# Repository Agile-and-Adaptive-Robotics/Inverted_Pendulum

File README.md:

# Inverted Pendulum

This repository contains the files related to the development, construction, and testing of the pneumatically-actuated Inverted Pendulum experimental rig, by members of the Agile & Adaptive Robotics Laboratory at Portland State University. The Inverted Pendulum was developed in tandem with the [Balance Platform](https://github.com/Agile-and-Adaptive-Robotics/Balance_Platform). The pair represents an experimental testbed for exploring perturbed bipedal stance, and was inspired by Peterka, 2002.

Note that this repo is for the pitured version of the Inverted Pendulum. The previous repo was archived and can be accessed [here] (https://github.com/Agile-and-Adaptive-Robotics/Inverted_Pendulum-archive). 

## Contents

- [Software](/code)
  - [README](/code/README.md)
- [datasheets](/datasheets)
  - [README](/datasheets/README.md)
- [pics](/pics)
- [SolidWorks](/SolidWorks)

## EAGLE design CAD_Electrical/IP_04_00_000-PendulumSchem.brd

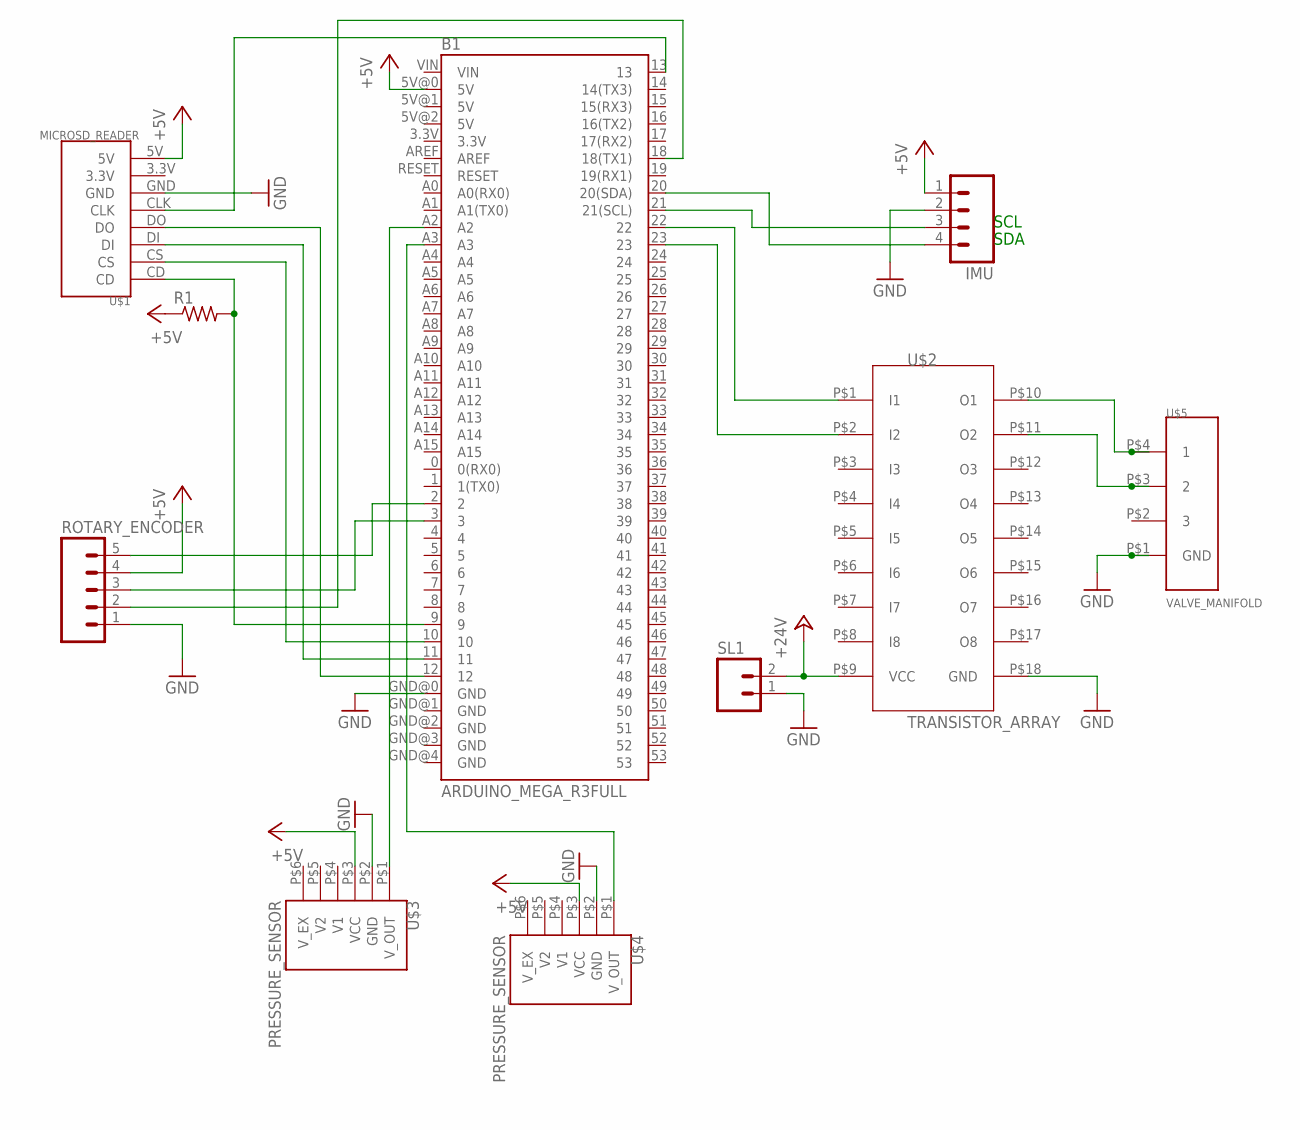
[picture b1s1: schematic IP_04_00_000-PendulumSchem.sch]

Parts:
B1: ARDUINO_MEGA_R3FULL; ARDUINO_MEGA
IMU: M04; 04P
R1: R-US_0204/7; 0204/7
ROTARY_ENCODER: M05; 05P
SL1: M02; 02P
U$1: MICROSD_READER
U$2: TRANSISTOR_ARRAY
U$3, U$4: PRESSURE_SENSOR
U$5: VALVE_MANIFOLD

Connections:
+5V: B1.5V@0 (5V), IMU.1, R1.1, ROTARY_ENCODER.4, U$1.5V, U$3.P$3 (VCC), U$4.P$3 (VCC)
+24V: SL1.2, U$2.P$9 (VCC)
GND: B1.GND@0 (GND), IMU.2, ROTARY_ENCODER.1, SL1.1, U$1.GND, U$2.P$18 (GND), U$3.P$2 (GND), U$4.P$2 (GND), U$5.P$1 (GND)
unnamed: B1.3, ROTARY_ENCODER.3
unnamed: B1.20 (20(SDA)), IMU.4
unnamed: B1.21 (21(SCL)), IMU.3
unnamed: B1.2, ROTARY_ENCODER.5
unnamed: B1.22, U$2.P$1 (I1)
unnamed: U$2.P$10 (O1), U$5.P$4 (1)
unnamed: B1.18 (18(TX1)), ROTARY_ENCODER.2
unnamed: U$2.P$11 (O2), U$5.P$3 (2)
unnamed: B1.23, U$2.P$2 (I2)
unnamed: B1.13, U$1.CLK
unnamed: B1.A2, U$3.P$1 (V_OUT)
unnamed: B1.12, U$1.DO
unnamed: B1.A3, U$4.P$1 (V_OUT)
unnamed: B1.11, U$1.DI
unnamed: B1.10, U$1.CS
unnamed: B1.9, R1.2, U$1.CD

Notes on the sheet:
SCL
SDA

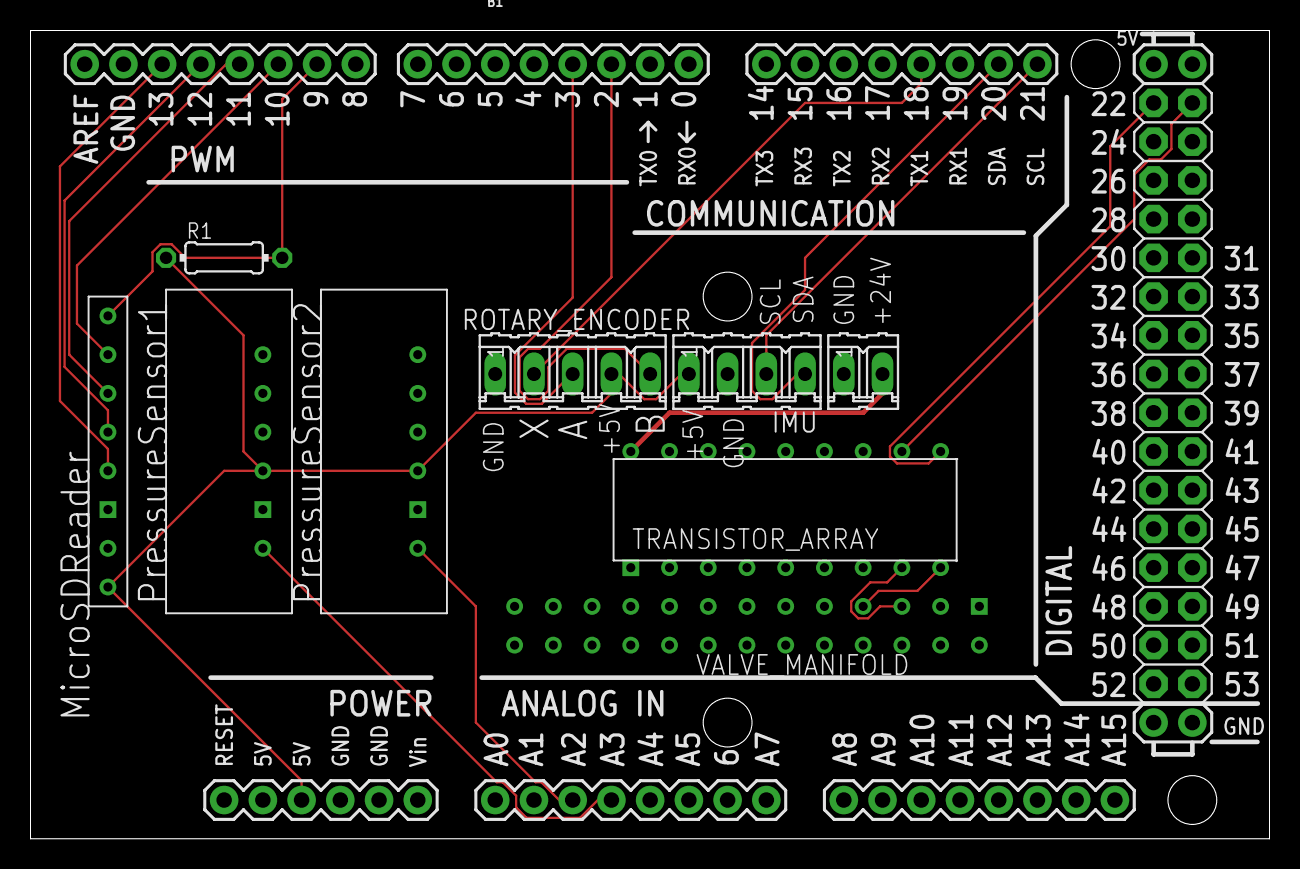
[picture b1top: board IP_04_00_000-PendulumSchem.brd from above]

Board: 2 copper layers, 81.3 x 53.0 mm, 10 parts (1 on the bottom side), 19 nets.

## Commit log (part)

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2020-06-13 Initial commit.
2020-06-14 Added DELETEME files.
2020-06-17 Added CAD assembly structures.
2020-06-17 Created basic foot base for designing main ankle joint.
    Will probably need to revise diameters? Appears to have odd proportions
2020-06-17 Same dimensions, split in half to fit on build plate (12in by 5in direction)
    In assembly, mirror around plane 1 from this part to get full build plate
2020-06-17 Created potential spool part
    This was mostly made as practice, very likely to change
2020-06-17 Fixed units to metric and extruded cuts for disc break
2020-06-17 McMaster-Carr hex bolt for base to balance plate
2020-06-17 Created tilapia joint, added mounting holes for tilapia to joint
2020-06-18 Added pulley for tendon string plus spool
2020-06-18 Modeled latch for disk break
    will need to decide if controlled by servo or switch before I create the rest of the mount. Also, will need gears to move string spool (& change shaft of spring to hex)
2020-06-18 Modified string spool to bevel gear top
    Removed disc brake because at such a small scale & low power, not necessary. Now can be controllable with rotary shaft & bevel gear
2020-06-18 Changed relations in independent bevel gear
2020-06-18 Switched sides for pulley mount
    This was done so that the tendon strings do not rub against the main shaft
2020-06-18 Created new tipia assembly, slotted tipia, added mounting holes to joint
2020-06-19 Began on double-axis attachment
    Explored two other somewhat feasible options for moveable attachments but could foresee that they added unnecessary complexity when moving into 2D adjustments
2020-06-19 Completed 1-axis adjustable attachment, prepared mounting piece for double axis
2020-06-19 Started vertical adjustment attachment
    Mostly done, will fill in mounting holes, shaft collars, etc. but for the most part ready for BPA CAD mount
2020-06-19 Added shaft collars to horizontal adjustment, shortened vertical shafts
    The more I design the vertical adjustment subassembly, the more I am convinced that I'll need to replace it with a threaded rod. Same concept but will be able to withstand gravity better, assuming th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
2020-06-22 Threaded rod adjustable attachments completed for 2-axis
    Still need to create mount for BPA to attachment piece. Also might shrink height of horizontal piece (unnecessarily bulky)
2020-06-22 Added mounting holes for attachment assembly
2020-06-23 Restored past progress from old bpaMount branch
    Changed type of lock nut to external teeth, inserted the BPA fitting into assembly
2020-06-23 Accidentally committed temporary files again
2020-06-23 Mounting holes and bolts
    Inserted threaded rod into BPA mount with nuts on ends. Reviewed mounting holes and fillets on all parts, and inserted all bolts (except fasteners to balance platform)
2020-06-23 Shifted tendon pulleys so no longer conflicting with attachment assembly
2020-06-23 Fixed locally referenced file
2020-06-25 Attached BPA attachment to sliding adjustment
2020-06-25 replaced round slider with square
2020-06-25 Replaced round slot with square slot
2020-06-28 Created IP assembly, fixed major tibia joint to fit with major foot joint, adjusted tibia mounting holes accordingly
2020-06-29 Added IMU symbol to schem
2020-06-29 Added servos to control tendon spool gear
2020-06-29 resolve conflicting files by copying these files from master
2020-06-29 Added transistory array & valve manifold datasheets.
2020-06-30 Inserted transistor array between arduino & valve manifold
2020-06-30 Added pressure sensor & IMU datasheets.
2020-06-30 Pressure sensors wired on A0, A1
2020-07-01 Disc brake for servo spool
2020-07-01 Servo mount
    Also deleted temp files
2020-07-01 Arduino Mount ATMEGA2560
2020-07-01 Servo mounting & servo files
2020-07-01 Began arduino mount with standoffs
2020-07-01 Finished arduino standoff spacing. Need to insert fasteners & possibly more spacers
2020-07-01 Split tibia in half, created weight attachment, added shaft collar from mcmaster
2020-07-01 Mounted pressure sensors
2020-07-03 Fixed footprints for each device
2020-07-03 Started arduino shield pcb
2020-07-06 Adjusted threaded rod and support shaft lengths
2020-07-06 Finished mounting holes for >5in adjustment
2020-07-06 Shortened handle extension
2020-07-06 Fixed shape of pins on PCB shield
2020-07-06 balance platform CAD stuff
2020-07-07 Created STL for 3D printed parts (first 3D printed iteration)
    Will change nuts on threaded rods to shaft collars because will be stripping threads on ends. Once those changes made, will pull request to master.
2020-07-07 Mounted shaft collars onto adjustable attachment assembly
2020-07-08 Foot base plate cutouts & threaded rod mount cutouts
    Went through multiple different cutout patterns (first random, then trapezoidal)
    Decided this version didn't sacrifice strength for saving material. Might need to widen a few of the bars though
2020-07-11 Cut Tibia in half, fixed mates
2020-07-13 Shortened tibia length
2020-07-15 Fixed encoder routing to interrupt & created ground plane
    Also inserted text, fixed footprints of custom devices, and replaced standard pins with screw terminals for more secure connection
2020-07-15 Shortened tibia, created mounting holes for weight attchment, added mechanical stop on tibia joint
2020-07-18 Standoff and handle STL
2020-07-20 Updated silkscreen to only part names plus external wires
2020-07-21 Fixed conflict issues
2020-07-21 Changed adjustment hex size to 7/16''
2020-07-21 This might be a view chnage but just in case
2020-07-21 Moved bearing file to tibia files
2020-07-21 remove temp files
2020-07-21 Shortened handle to remove conflict with plate & adjusted main joint for bearing
2020-07-23 Cut down tibia width, BPA adjustment holder width, remated everything
2020-07-23 Widened 24V connection & Deleted extraneous holes & MicroSD added
2020-07-23 Found IMU Libraries
    https://learn.adafruit.com/nxp-precision-9dof-breakout/arduino-code
2020-07-23 Added bushings and replaced bearings
2020-07-27 Reorganized & restored foot files to #17
2020-07-27 Reduced width of main joint
2020-07-27 Timer interrupt set-up for MEGA
2020-07-28 Rotary encoder device syntax
2020-07-29 Fixed library folder with rotary encoder
2020-07-29 Created branch
2020-07-29 placed nut holes
2020-07-29 Changed bushing position
2020-07-29 Deletes temp files
2020-07-30 Started mapping mega2560 pins
2020-07-30 Manual PWM with delays. AnalogRead of pressure sensors.
2020-08-04 Revert "temporarily remove this file to resolve the conflict."
    This reverts commit 91f06de7276bcdfa5c47d5ee676213101accdbd6.
2020-08-04 bring changes of the Tibia from the printingAndCoding-ReynaAy branch to restore the main assembly file.
2020-08-04 update the final assembly file to resolve conflict
2020-08-05 Creating pwm based on millis timekeeper
2020-08-05 Fixed out of scope vars
2020-08-05 Creating multiple options for pwm signal generation
    Unable to run with electronic sensors at home so instead creating options where people can take my code and use whichever pwm generation works best for them
2020-08-05 Resized tibia joint holes, shrunk the shaft length
2020-08-05 Pocketed the tibia joint
2020-08-19 Created cutouts for bracket, pocketed tibia, shortened BPA adjustments, deleted bushings, shrunk shaft holes
2020-08-19 temp files
2022-06-21 Added a test Arduino file
2022-06-21 updated IP_01_01_03
    less side to side play.
2022-06-22 small
    no change, just printed.
2022-06-22 Worked on getting the position from the encoder and made a second file for testing different aspects of the project.
2022-06-23 Made gyro absolute angle calculation code.
2022-06-23 baseplate save
    print setup
2022-06-23 Combined most aspects into Gyto-test for testing.
2022-06-23 Fixing various aspects of code.
2022-06-24 stl folder
2022-06-24 stl swap
2022-06-24 updated baseplate
2022-06-24 Combined one-off with full simulation so that it uses varying on/off frequencies to open and close the valve manifold.
2022-06-25 Fixed a problem with what I just did.
2022-06-27 new pulley wheel
2022-06-27 Didn't do much. Just tweaked some things and tried to find out what was wrong with the IMU.
2022-06-28 20mm bpa pulley
2022-06-29 Wrote balance platform code.
    There are three settings:
    - random: moves to random angles
    - high-to-low: moves from side to side
    - manual: moves based on input from a potentiometer
2022-06-30 Mostly worked on balance platform code and a bit on starting BPA microcontroller code.
2022-06-30 29th
    changes in cad
2022-07-06 connector plate
    made a plate and rearranged the bolts
2022-07-07 no change
    remove auto save
2022-07-08 Worked on transferring data from one Arduino to another.
2022-07-08 base change
    base change
    + valve(IP_03_01_001)
2022-07-08 smoothing
    made it smooth(ish)
2022-07-08 last of the day
2022-07-11 valve holder
2022-07-11 code
2022-07-12 gyro
2022-07-12 Wrote code for inverted pendulum with gyro sensor.
2022-07-13 started new feet based on 8020
2022-07-14 Worked on converting assembly code to opcodes.
2022-07-18 Worked on ISP program further, wrote new code for balance platform, moved documentation to GitHub folder.
2022-07-19 remove autosave
2022-07-19 Worked on daisy chaining strategy for ISP.
2022-07-25 stl of parts
2022-07-27 Added pressure sensor functionality to Pressure_Changer_Gyro, got balance platform to work with new code, started planning out code for a BPA board.
2022-07-28 worked on the spring spool.
2022-08-01 spring
2022-08-02 Made ode implementing Stu's idea for the inverted pendulum. Made tweaks to normal balancing inverted pendulum code and balancing platform code.
2022-08-06 Updated code to work with new inverted pendulum setup.
2022-08-06 fixed it
2022-08-11 Updated inverted pendulum code for new design.
2022-08-12 Made ball socket and started tibia.
2022-08-12 Made tibia connector.
2022-08-12 ball
2022-08-15 foot changes
2022-08-16 rearrange files
2022-08-19 first working test
2022-08-19 Made new muscle control code with PWM.
2022-08-29 Worked on PWM Assembly with microchip studio.
2022-09-02 Made new tibia controllable through accelerometer.
2022-09-19 clean_finished
2022-09-19 started foot joints
2022-09-21 added mid foot and toe
2022-09-29 made paths for string
2022-10-01 Starting working on new foot muscle controls.
2022-10-16 smoothing
    smoothed all parts and started 10mm bpa mount.
2023-05-11 Added gitignore.
2023-05-11 Removed unnecessary files.
2023-05-12 Shortening file names.
2023-06-23 Added media
    Added media files that Amiri made for inverted pendulum (IP) v2
2024-04-20 setota_commits
    These are on my account for some reason. I will publish her branch.
2024-04-20 pack n play
    For the biomimetic assembly
2024-04-26 Reapply "Updated inverted pendulum code for new design."
    This reverts commit 86ff3b593088ae134fa0d0166710bccda351dd66.
2024-06-20 Motor Connector to Lead Screw
    Changes to original design with anti-slip measures.
2024-06-26 Update CAD files and progress on Design
2024-06-26 Organization and new base assembly
2024-07-01 Modified the frame and changed orientation of pieces on the base plate
2024-07-09 Added Constraints and variables cheat sheet
2024-07-09 Updated the sheet version, with more configurations and options.
2024-07-11 More configurations added to constraints and variables list, and a list of parts added to the same sheet.
2024-07-17 Made rack and pinion base design
2024-07-18 Re-organized parts and re-did assemblys
2024-07-19 Updated Assemblies and did proper mates
2024-07-31 Pinion Gear and Support Changed - Ashton
2024-08-01 Re-organized files and cleaned up duplicates - Ashton
2024-08-01 pablo
2024-08-01 Main Assembly Mates
2024-08-05 First version of finalized CAD
2024-08-05 Change? -Ashton
2024-08-05 First version of finalized CAD - Pablo
2024-08-05 rut ro
2024-08-06 hope v2
2024-08-06 Pinion Design Update
2024-08-06 Fixed mates and assemblies
2024-08-06 pinion gear update test2
2024-08-06 reverting mistakes
2024-08-06 Created the layered pinion
2024-08-06 Moved pinion layers into folder
2024-08-07 yipyip hooray
2024-08-07 clearance
2024-08-07 Added support for motor and screw holes
2024-08-07 more
2024-08-07 Filleted sharp edges on pinion gear
2024-08-08 Fixed Rebuild errors

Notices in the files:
parts and their libraries:
SparkFun-Boards-deleted2holes: Licensing: Creative Commons ShareAlike 4.0 International - https://creativecommons.org/licenses/by-sa/4.0
